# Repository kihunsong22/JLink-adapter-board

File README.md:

# JLink-adapter-board
JLink adapter board with most used connectors

### List of Connectors
* 2.54mm 2*10 pin female socket connector (for connecting to J-Link)
* 2.54mm 2*10 pin IDC male header connector
* 2.54mm 2*5 pin IDC male header connector
* 2.00mm 2*5 pin IDC male header connector
* 1.27mm 2*5 pin IDC male header connector (supports both SMD and PTH)
* 2.54mm 2*3 pin IDC male header connector - for Tag-Connect cable: [TC2030-IDC-NL](https://www.tag-connect.com/product/tc2030-idc-nl)
* 2.54mm 4 pin XH2.54 connector
* 2.54mm 6 pin XH2.54 connector

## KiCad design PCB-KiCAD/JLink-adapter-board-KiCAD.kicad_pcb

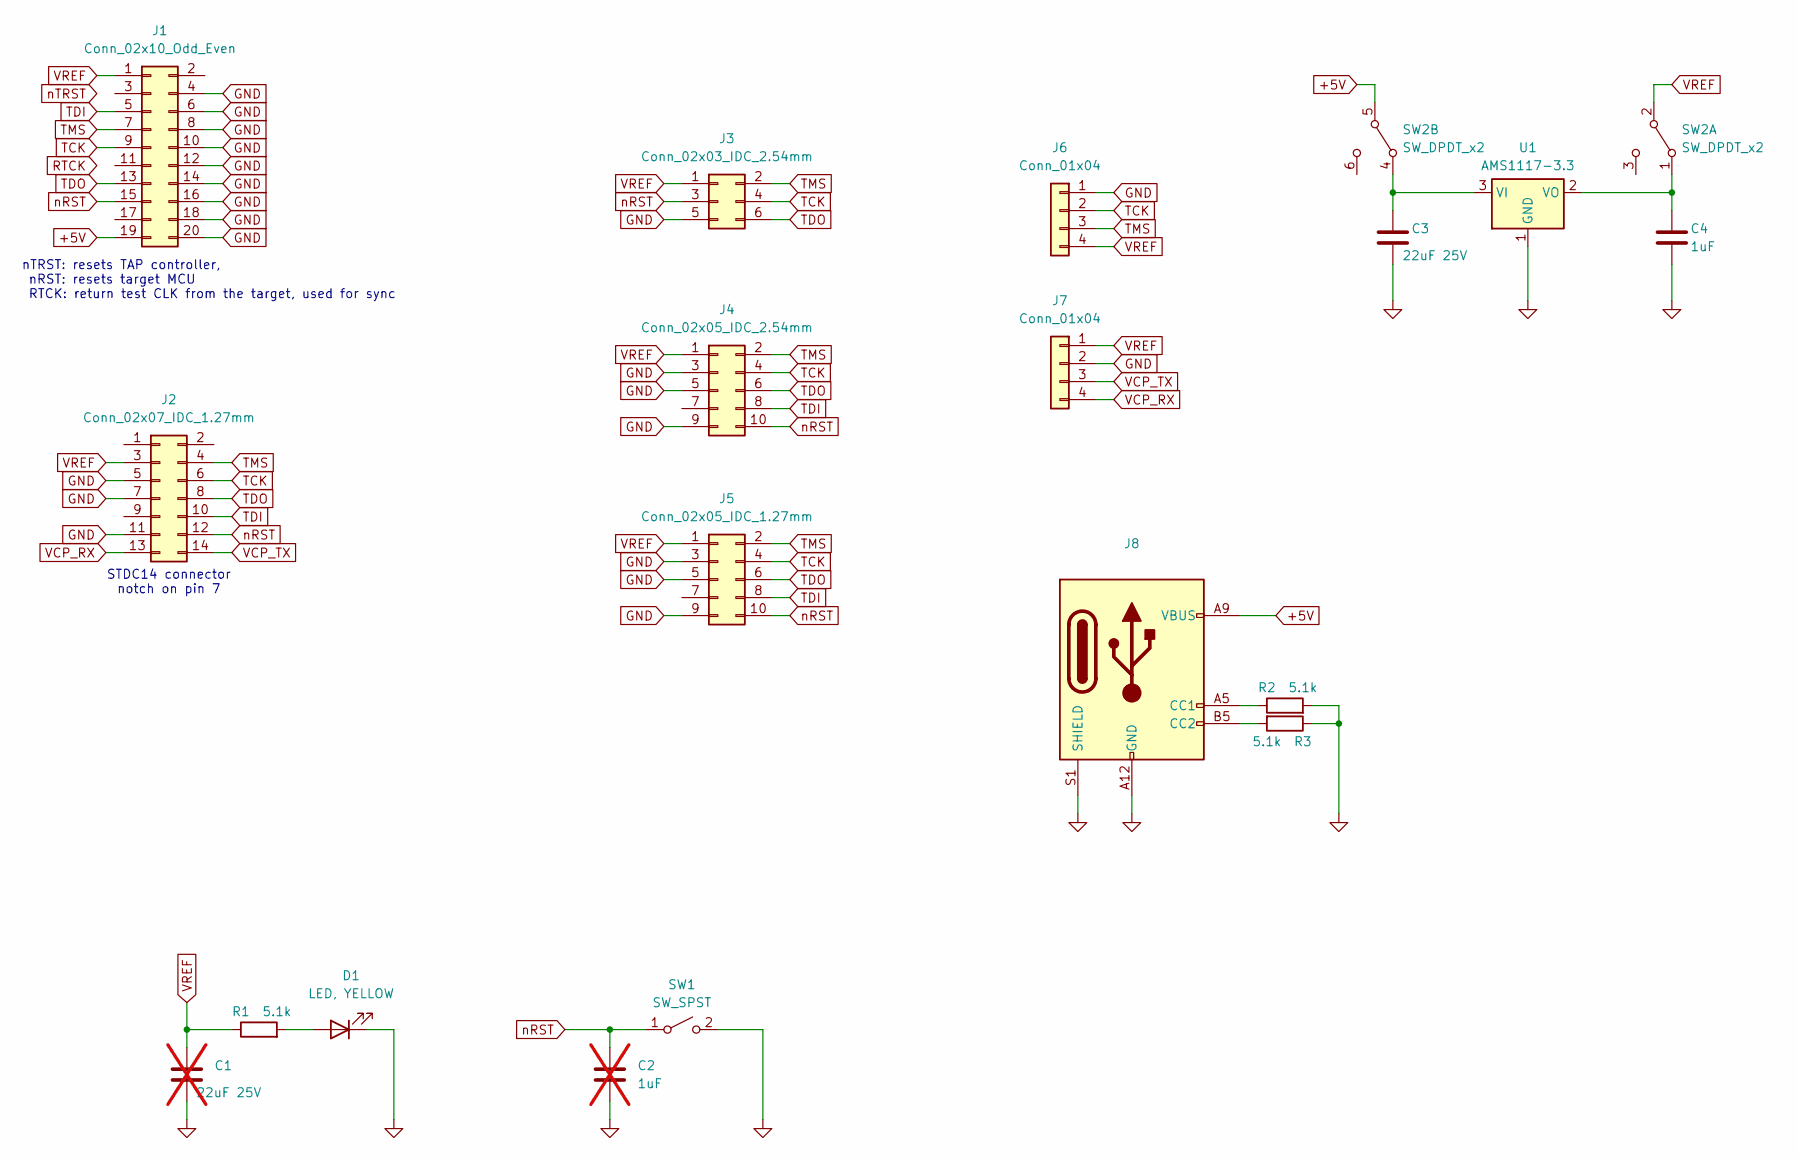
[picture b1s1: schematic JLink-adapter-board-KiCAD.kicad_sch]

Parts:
C1: 22uF 25V; C_0805_2012Metric; LCSC C45783; not fitted
C2: 1uF; C_0402_1005Metric; LCSC C52923; not fitted
C3: 22uF 25V; C_0805_2012Metric; LCSC C45783
C4: 1uF; C_0402_1005Metric; LCSC C52923
D1: LED, YELLOW; LED_0603_1608Metric; LCSC C72038
J1: Conn_02x10_Odd_Even; 2X10-2.54MM-END-LAUNCH; LCSC-notab C92266
J2: Conn_02x07_IDC_1.27mm; PinHeader_2x07_P1.27mm_Vertical; LCSC C2935955
J3: Conn_02x03_IDC_2.54mm; IDC-Header_2x03_P2.54mm_Vertical; LCSC C5372863
J4: Conn_02x05_IDC_2.54mm; IDC-Header_2x05_P2.54mm_Vertical; LCSC C5665
J5: Conn_02x05_IDC_1.27mm; PinHeader_2x05_P1.27mm_Vertical; LCSC C2962228
J6, J7: Conn_01x04; JST_XH_B4B-XH-A_1x04_P2.50mm_Vertical; LCSC C37815
J8: USB_C_Receptacle_PowerOnly_6P; USB_C_Receptacle_HRO_TYPE-C-31-M-17; LCSC C283541
R1, R2, R3: 5.1k; R_0402_1005Metric; LCSC C25905
SW1: SW_SPST; SW_Push_1P1T_XKB_TS-1187A; LCSC C318884
SW2: SW_DPDT_x2; DPDT-AYZ0202; LCSC C318998
U1: AMS1117-3.3; SOT-89-3; LCSC C5120796

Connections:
+5V: J1.19, J8.A9 (VBUS), J8.B9 (VBUS), SW2.5 (B)
GND: C1.2, C2.2, C3.2, C4.2, D1.1 (K), J1.4, J1.6, J1.8, J1.10, J1.12, J1.14, J1.16, J1.18, J1.20, J2.5, J2.7, J2.11, J3.5, J4.3, J4.5, J4.9, J5.3, J5.5, J5.9, J6.1, J7.2, J8.A12 (GND), J8.B12 (GND), J8.S1 (SHIELD), R2.2, R3.1, SW1.2 (B), U1.1 (GND)
unnamed: D1.2 (A), R1.2
unnamed: J8.A5 (CC1), R2.1
unnamed: J8.B5 (CC2), R3.2
unnamed: C4.1, SW2.1 (A), U1.2 (VO)
unnamed: C3.1, SW2.4 (A), U1.3 (VI)
TCK: J1.9, J2.6, J3.4, J4.4, J5.4, J6.2
TDI: J1.5, J2.10, J4.8, J5.8
TDO: J1.13, J2.8, J3.6, J4.6, J5.6
TMS: J1.7, J2.4, J3.2, J4.2, J5.2, J6.3
VCP_RX: J2.13, J7.4
VCP_TX: J2.14, J7.3
VREF: C1.1, J1.1, J2.3, J3.1, J4.1, J5.1, J6.4, J7.1, R1.1, SW2.2 (B)
nRST: C2.1, J1.15, J2.12, J3.3, J4.10, J5.10, SW1.1 (A)

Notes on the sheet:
nTRST: resets TAP controller, nRST: resets target MCU RTCK: return test CLK from the target, used for sync
STDC14 connector notch on pin 7

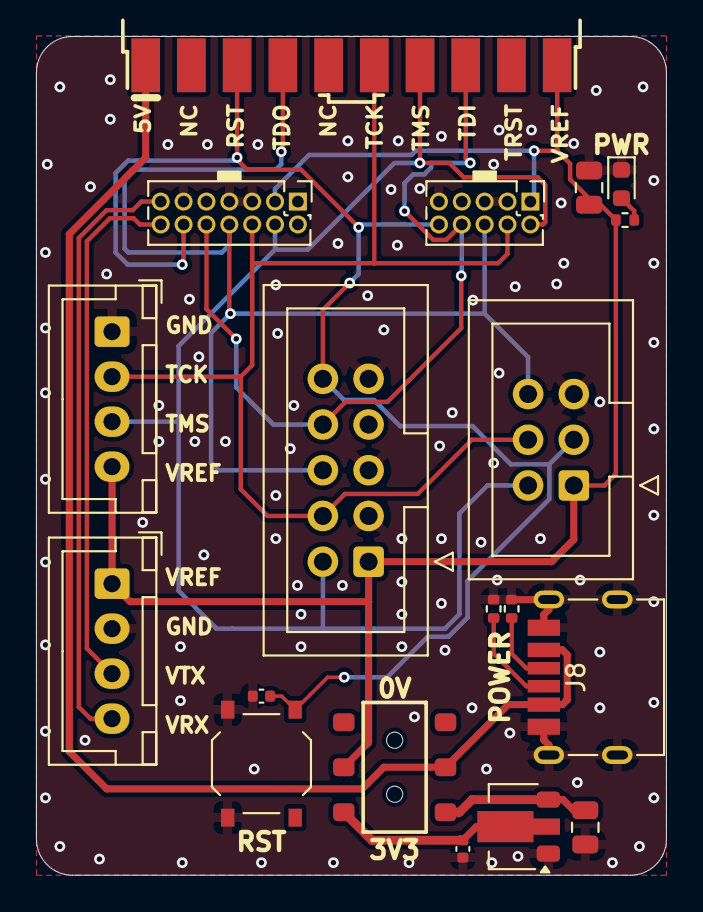
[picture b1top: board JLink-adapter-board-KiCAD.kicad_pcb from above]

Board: 2 copper layers, 35.0 x 46.6 mm, 19 parts (0 on the bottom side), 15 nets.

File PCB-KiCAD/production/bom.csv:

Designator,Footprint,Quantity,Value,LCSC Part #
C3,0805,1,22uF 25V,C45783
C4,0402,1,1uF,C52923
D1,0603,1,"LED, YELLOW",C72038
J1,2X10-2.54MM-END-LAUNCH,1,Conn_02x10_Odd_Even,
J2,PinHeader_2x07_P1.27mm_Vertical,1,Conn_02x07_IDC_1.27mm,C2935955
J3,IDC-Header_2x03_P2.54mm_Vertical,1,Conn_02x03_IDC_2.54mm,C5372863
J4,IDC-Header_2x05_P2.54mm_Vertical,1,Conn_02x05_IDC_2.54mm,C5665
J5,PinHeader_2x05_P1.27mm_Vertical,1,Conn_02x05_IDC_1.27mm,C2962228
"J6, J7",JST_XH_B4B-XH-A_1x04_P2.50mm_Vertical,2,Conn_01x04,C37815
J8,USB_C_Receptacle_HRO_TYPE-C-31-M-17,1,USB_C_Receptacle_PowerOnly_6P,C283541
"R1, R2, R3",0402,3,5.1k,C25905
SW1,SW_Push_1P1T_XKB_TS-1187A,1,SW_SPST,C318884
SW2,DPDT-AYZ0202,1,SW_DPDT_x2,C318998
U1,SOT-89-3,1,AMS1117-3.3,C5120796

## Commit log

2020-04-06 moved repo
2020-04-07 V1.1
2020-04-13 V1.2
2020-04-13 added pics, updated README
2020-04-13 compressed pics
2020-04-13 fixed weird text angle
2020-04-22 changed font size
2020-04-22 updated README for V1.2
2020-04-22 V1.3 - changed text orientation
2020-05-01 connected pin 5, 9 to GND
2020-05-15 changed right angle connector to end launch
2020-05-27 fixed footprint error
2020-08-01 V1.5
    - changed RST to TDI for 3*2 pin connector
    - optimized routing
2021-02-03 rollback to V1.4
2021-07-04 V1.6 update
2024-12-26 DNP'd capacitors to not reset target board, fixed connector part links
2025-07-16 removed temporary files and backups
2025-07-16 update .gitignore with KiCAD options
